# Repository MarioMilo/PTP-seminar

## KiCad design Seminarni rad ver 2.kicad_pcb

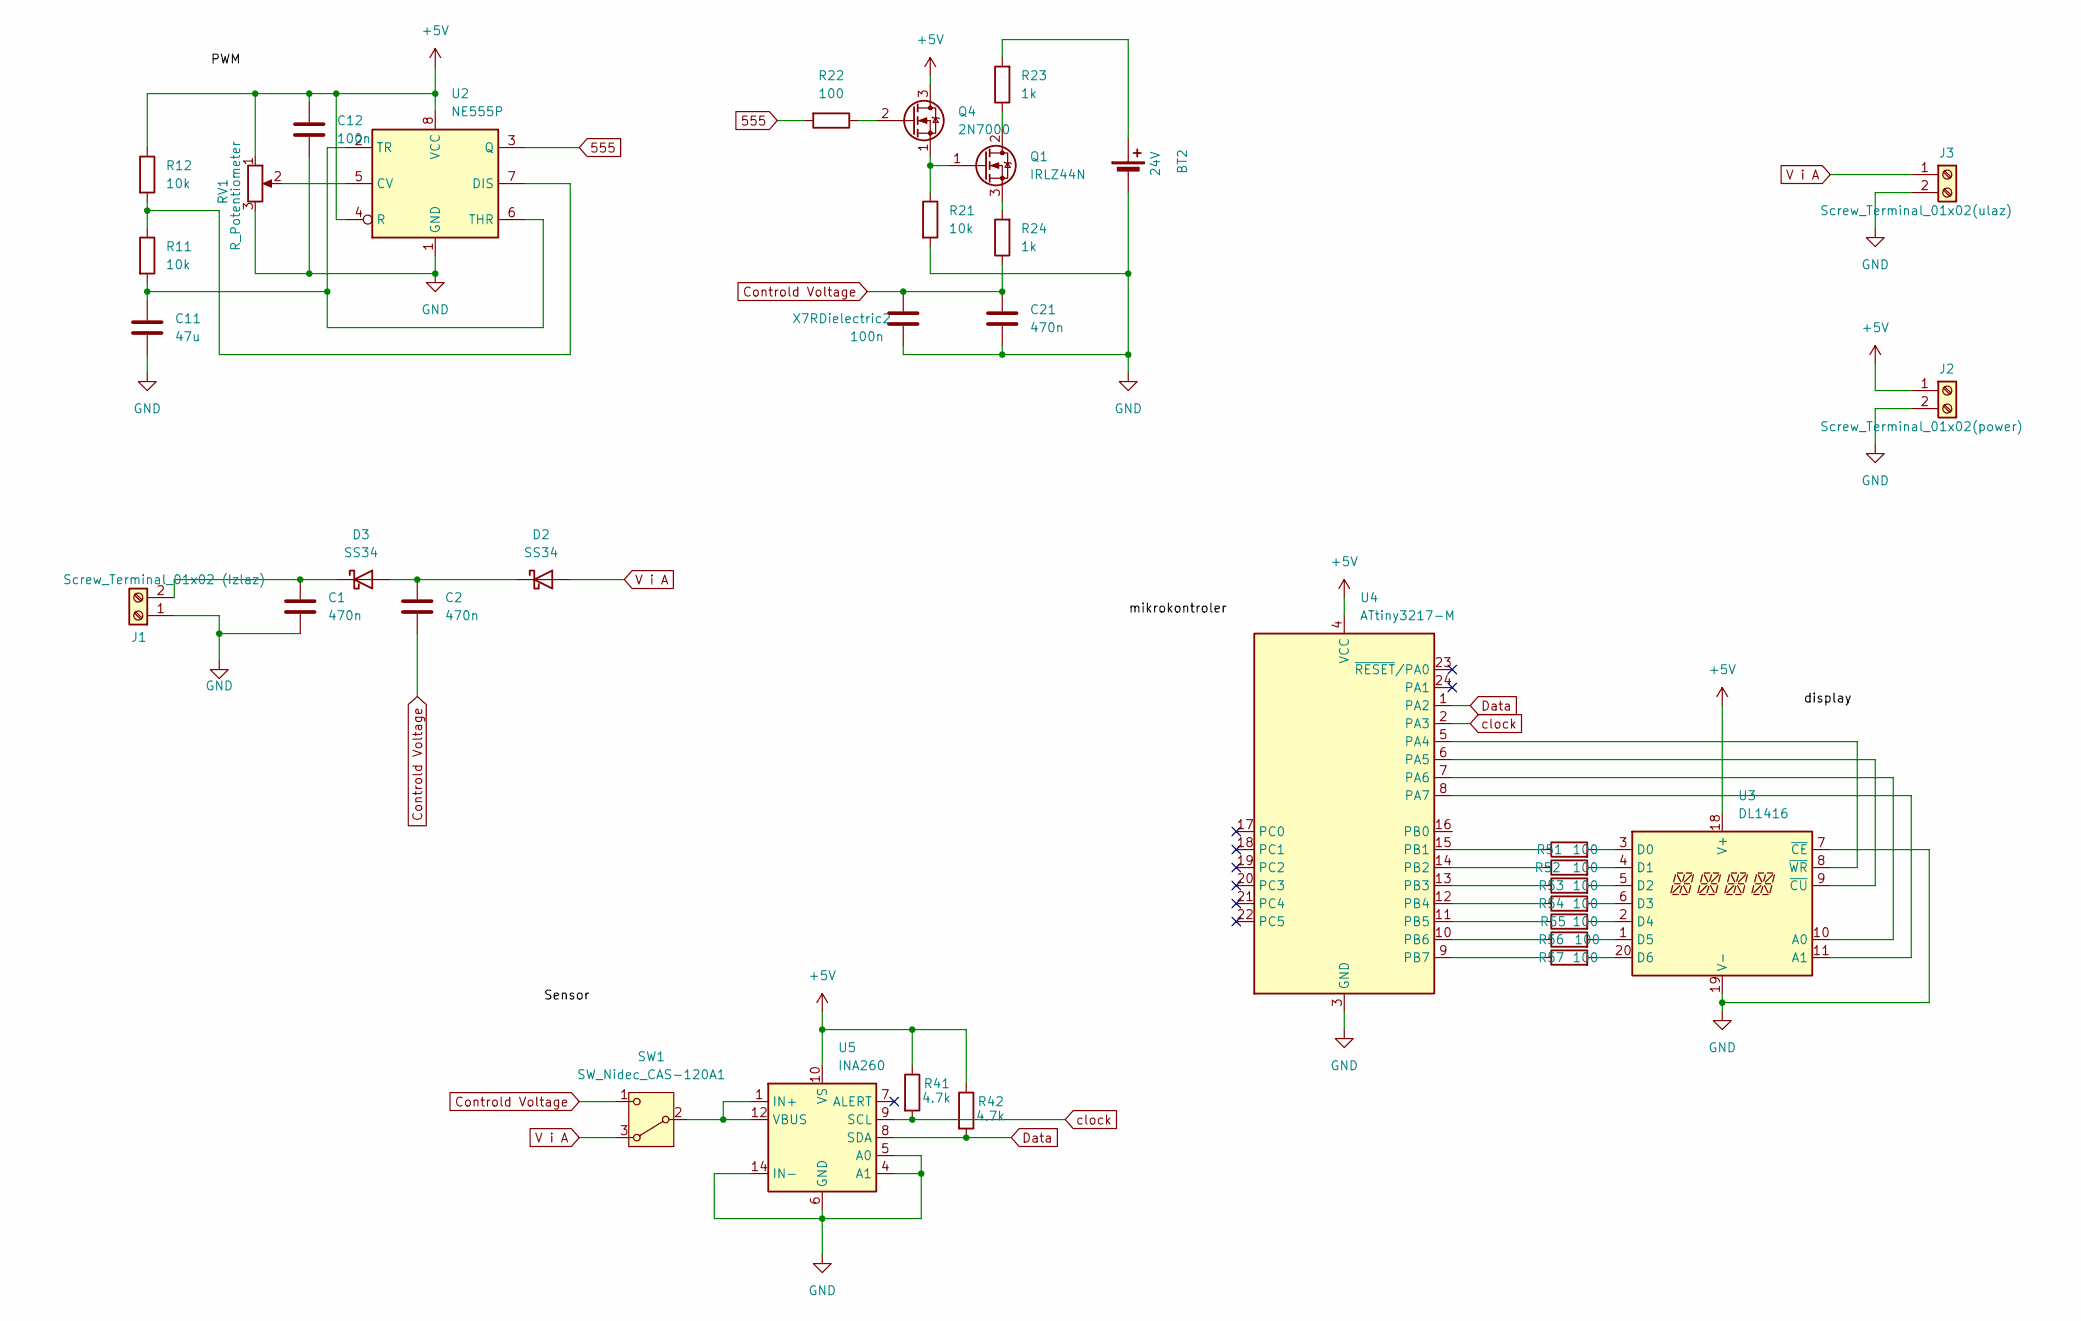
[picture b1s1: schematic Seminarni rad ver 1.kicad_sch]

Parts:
BT2: 24V; BatteryHolder_MYOUNG_BS-07-A1BJ001_CR2032
C1, C2, C21: 470n; C_0603_1608Metric
C11: 47u; C_0603_1608Metric
C12: 100n; C_0603_1608Metric
D2, D3: SS34; D_SMA
J1: Screw_Terminal_01x02 (Izlaz); TerminalBlock_Xinya_XY308-2.54-2P_1x02_P2.54mm_Horizontal
J2: Screw_Terminal_01x02(power); TerminalBlock_Xinya_XY308-2.54-2P_1x02_P2.54mm_Horizontal
J3: Screw_Terminal_01x02(ulaz); TerminalBlock_Xinya_XY308-2.54-2P_1x02_P2.54mm_Horizontal
Q1: IRLZ44N; TO-220-3_Vertical
Q4: 2N7000; TO-92_Inline
R11, R12, R21: 10k; R_MELF_MMB-0207
R22, R51, R52, R53, R54, R55, R56, R57: 100; R_MELF_MMB-0207
R23, R24: 1k; R_MELF_MMB-0207
R41, R42: 4.7k; R_MELF_MMB-0207
RV1: R_Potentiometer; Potentiometer_ACP_CA6-VSMD_Vertical_Hole
SW1: SW_Nidec_CAS-120A1; Nidec_Copal_CAS-120A
U2: NE555P; DIP-8_W7.62mm
U3: DL1416
U4: ATtiny3217-M; QFN-24-1EP_4x4mm_P0.5mm_EP2.6x2.6mm
U5: INA260; TSSOP-16_4.4x5mm_P0.65mm
X7RDielectric2: 100n; C_1206_3216Metric_Pad1.33x1.80mm_HandSolder

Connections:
555: R22.2, U2.3 (Q)
+5V: C12.1, J2.1, Q4.3 (D), R12.1, R41.1, R42.1, RV1.1, U2.4 (R), U2.8 (VCC), U3.18 (V+), U4.4 (VCC), U5.10 (VS)
Controld Voltage: C2.2, C21.1, R24.1, SW1.1 (C), X7RDielectric2.1
Data: R42.2, U4.1 (PA2), U5.8 (SDA)
GND: BT2.2 (-), C1.2, C11.2, C12.2, C21.2, J1.1, J2.2, J3.2, R21.2, RV1.3, U2.1 (GND), U3.7 (~CE), U3.19 (V-), U4.3 (GND), U4.25 (GND), U5.4 (A1), U5.5 (A0), U5.6 (GND), U5.11 (GND), U5.14 (IN-), U5.15 (IN-), U5.16 (IN-), X7RDielectric2.2
unnamed: BT2.1 (+), R23.2
unnamed: C2.1, D2.1 (K), D3.2 (A)
unnamed: C1.1, D3.1 (K), J1.2
unnamed: Q1.2 (D), R23.1
unnamed: Q1.1 (G), Q4.1 (S), R21.1
unnamed: Q1.3 (S), R24.2
unnamed: Q4.2 (G), R22.1
unnamed: SW1.2 (B), U5.1 (IN+), U5.2 (IN+), U5.3 (IN+), U5.12 (VBUS)
unnamed: RV1.2, U2.5 (CV)
unnamed: R11.1, R12.2, U2.7 (DIS)
unnamed: C11.1, R11.2, U2.2 (TR), U2.6 (THR)
unnamed: U3.10 (A0), U4.7 (PA6)
unnamed: U3.11 (A1), U4.8 (PA7)
unnamed: R51.2, U3.3 (D0)
unnamed: R52.2, U3.4 (D1)
unnamed: R53.2, U3.5 (D2)
unnamed: R54.2, U3.6 (D3)
unnamed: R55.2, U3.2 (D4)
unnamed: R56.2, U3.1 (D5)
unnamed: R57.2, U3.20 (D6)
unnamed: U3.9 (~CU), U4.6 (PA5)
unnamed: U3.8 (~WR), U4.5 (PA4)
unnamed: R51.1, U4.15 (PB1)
unnamed: R52.1, U4.14 (PB2)
unnamed: R53.1, U4.13 (PB3)
unnamed: R54.1, U4.12 (PB4)
unnamed: R55.1, U4.11 (PB5)
unnamed: R56.1, U4.10 (PB6)
unnamed: R57.1, U4.9 (PB7)
V i A: D2.2 (A), J3.1, SW1.3 (A)
clock: R41.2, U4.2 (PA3), U5.9 (SCL)

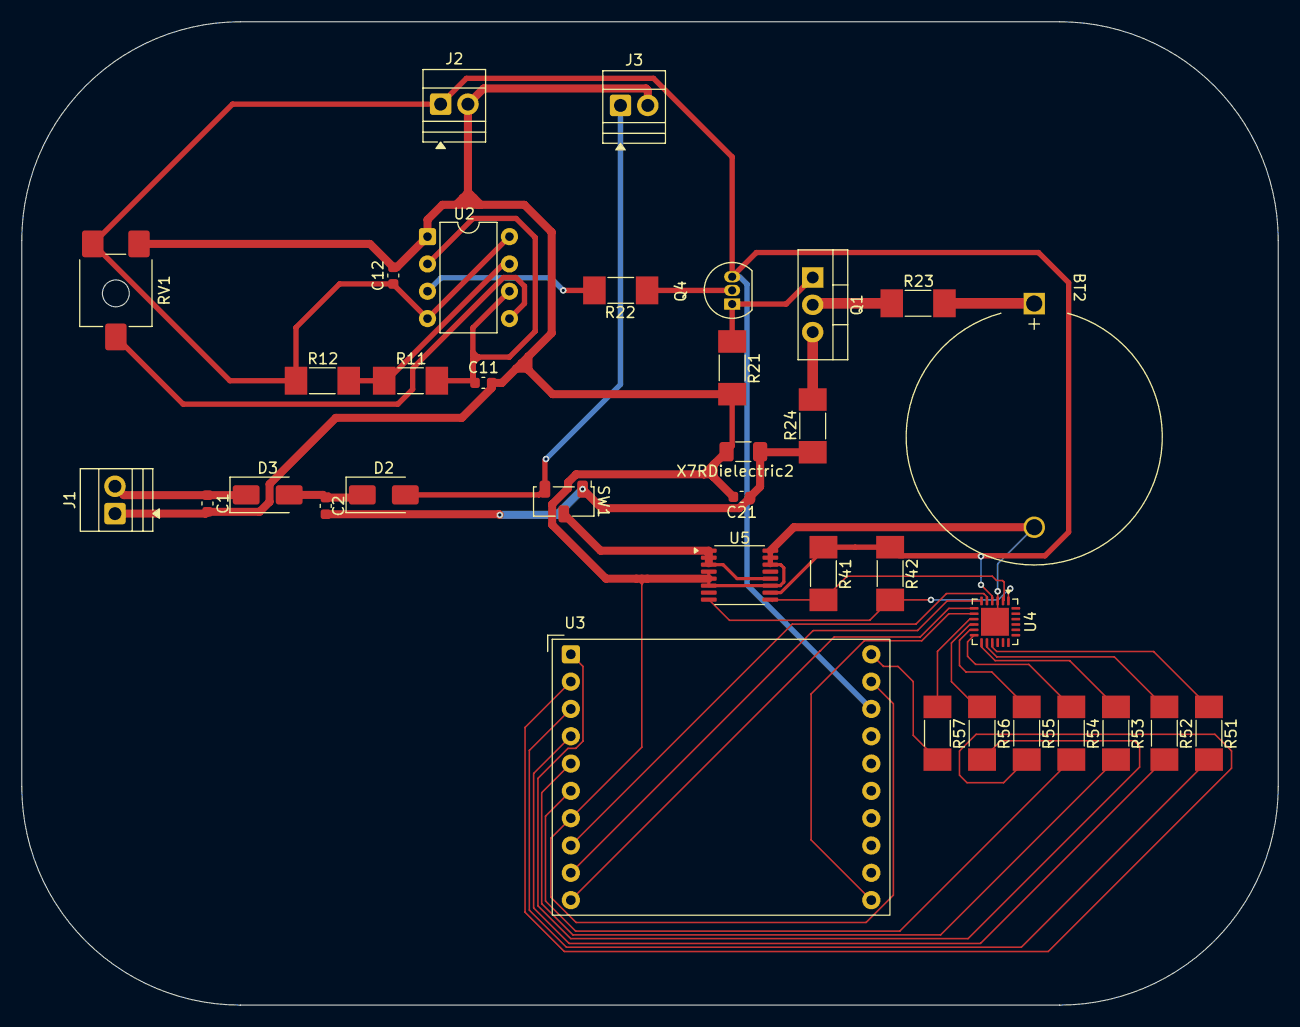
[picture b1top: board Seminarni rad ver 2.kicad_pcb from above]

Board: 2 copper layers, 116.8 x 91.4 mm, 35 parts (0 on the bottom side), 36 nets.

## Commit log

2026-06-29 chanege
2026-06-29 chande
